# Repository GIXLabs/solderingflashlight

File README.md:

These are the files used in the intro to soldering workshop where students come away with a working (hopefully) flashlight keychain.

# Bill of Materials
* CR2032 battery
* CR2032 battery holder
* Standard 5 mm LED
* 6 mm tactile switch
* 3D printed enclosure
* PCB made using .brd file

# Parameters for PCB
* 1.6 mm board thickness
* ENIG - ROHS
* Remove order number

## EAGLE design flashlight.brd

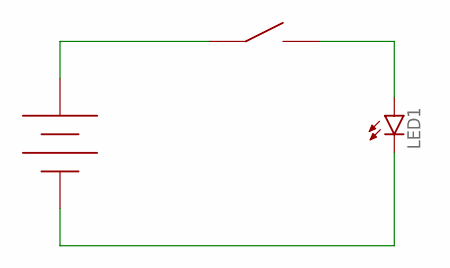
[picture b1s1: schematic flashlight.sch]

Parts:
LED1: LED5MM
U$1: 2032HOLDER
U$2: TACT_SWITCH

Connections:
unnamed: U$1.POS, U$2.1, U$2.2 (1)
unnamed: LED1.A, U$2.3, U$2.4 (3)
unnamed: LED1.K (C), U$1.NEG

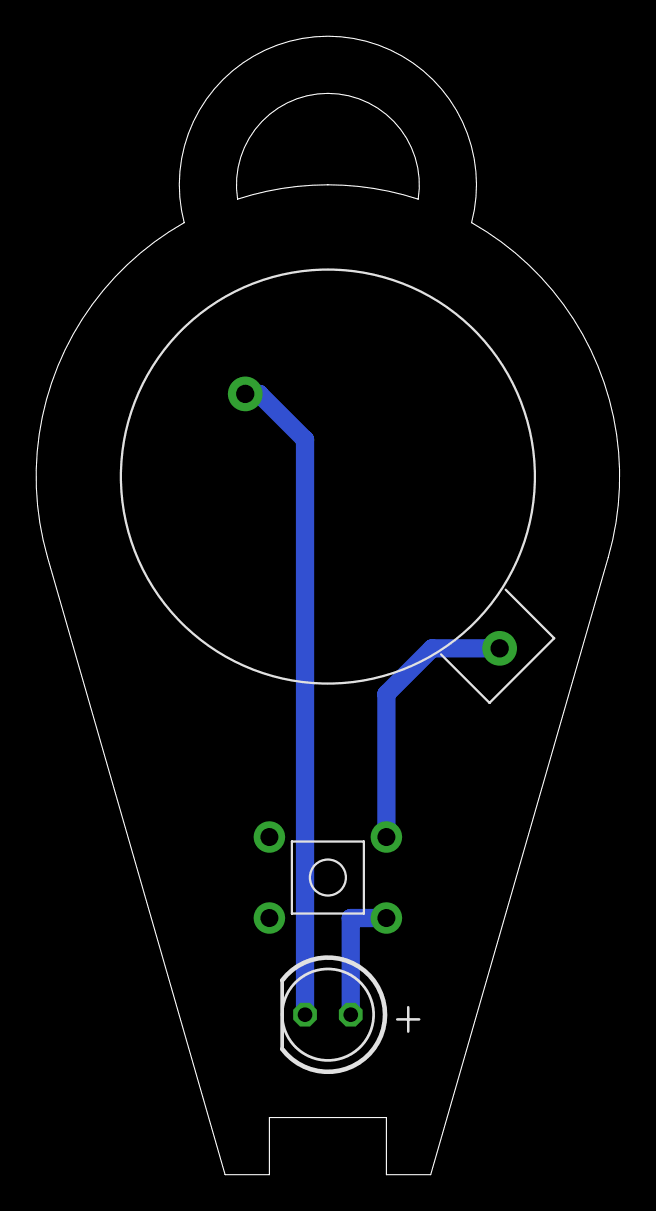
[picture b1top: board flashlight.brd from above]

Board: 2 copper layers, 32.4 x 63.2 mm, 3 parts (0 on the bottom side), 3 nets.

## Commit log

2022-08-01 Initial commit of working board.
2022-12-16 Added enclosure Fusion files.
